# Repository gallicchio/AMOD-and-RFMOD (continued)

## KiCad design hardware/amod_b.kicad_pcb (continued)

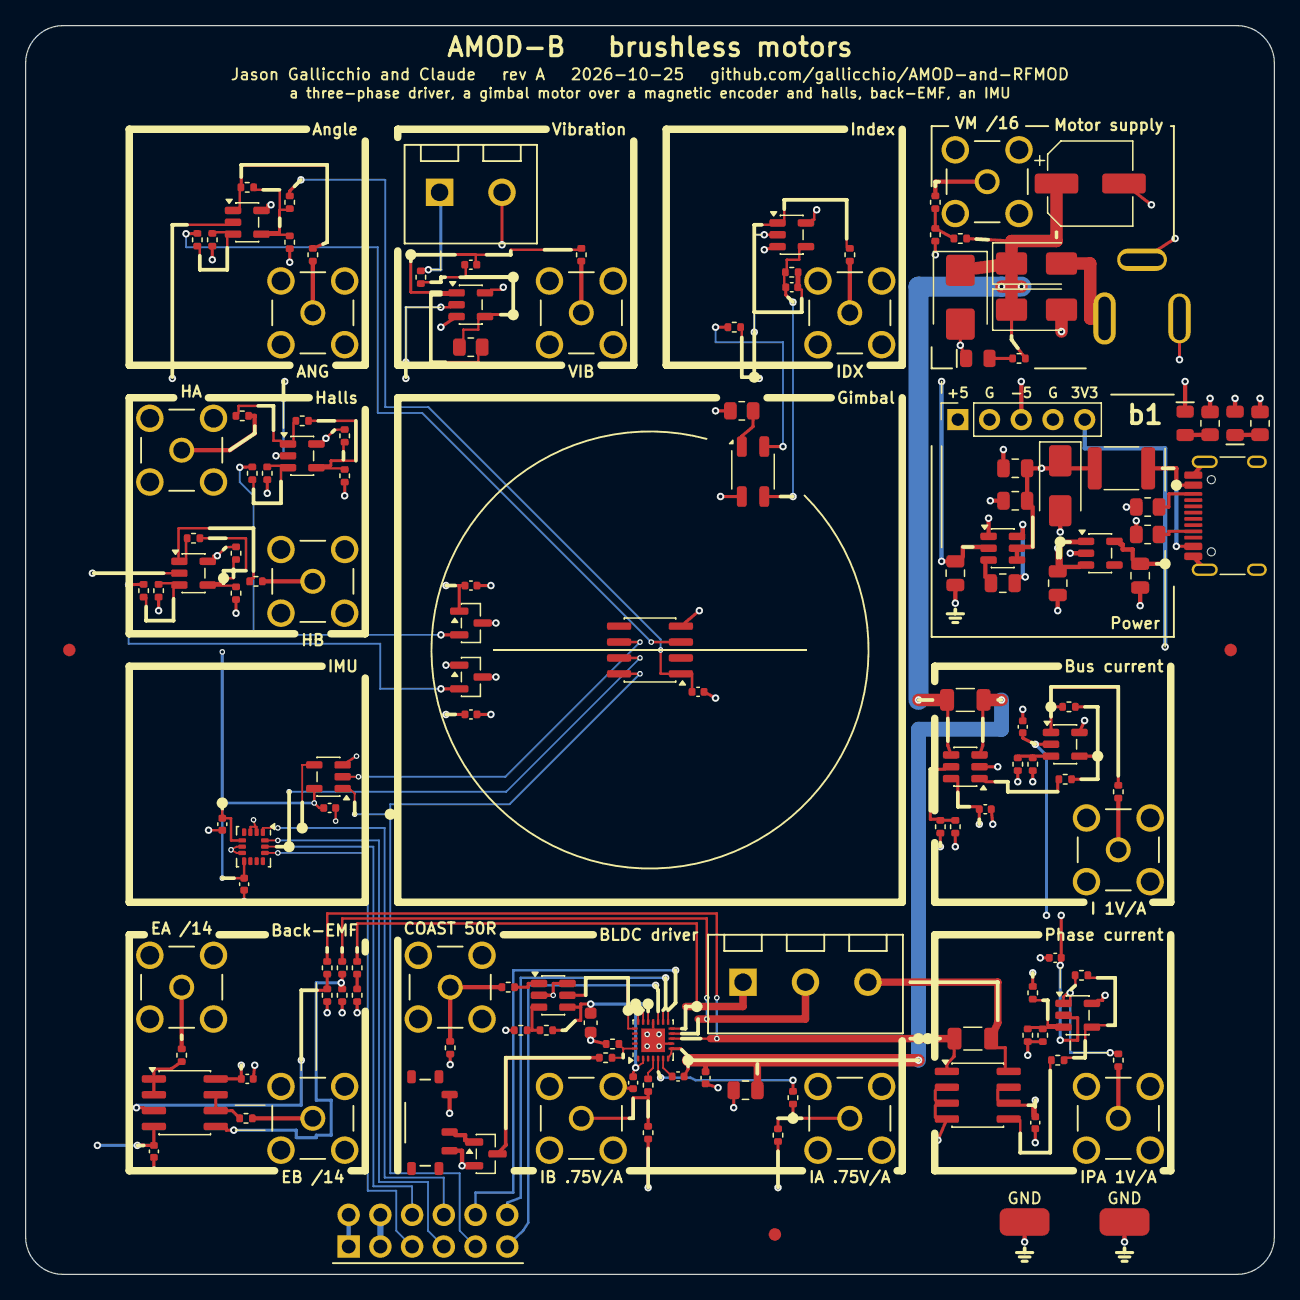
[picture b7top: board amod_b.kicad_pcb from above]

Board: 4 copper layers, 100.0 x 100.0 mm, 147 parts (0 on the bottom side), 86 nets.

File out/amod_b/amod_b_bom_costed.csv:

Comment,Designator,Footprint,LCSC Part #,MPN,Qty,Unit $,Ext $,JLC
220u,C201,CP_Elec_6.3x7.7,C2992606,XT220UF25V90RV0075,1,0.0534,0.053,extended
1u,C304,C_0603_1608Metric,C15849,CL10A105KB8NNNC,1,0.0146,0.015,basic
1n,C801,C_0402_1005Metric,C1523,0402B102K500NT,1,0.0038,0.004,basic
100p,C901,C_0402_1005Metric,C1546,0402CG101J500NT,1,0.0033,0.003,basic
1u,"C105,C106",C_0805_2012Metric,C28323,CL21B105KBFNNNE,2,0.0341,0.068,basic
10u,"C101,C102,C103,C104,C302",C_0805_2012Metric,C15850,CL21A106KAYNNNE,5,0.0426,0.213,basic
100n,"C301,C303,C305,C401,C402,C501,C502,C503,C601,C602,C603,C1101,C1102,C1201,C1202",C_0402_1005Metric,C1525,CL05B104KO5NNNC,15,0.0035,0.052,basic
SMAJ5.0A,D101,D_SMA,C78401,SMAJ5.0A,1,0.0537,0.054,extended
SMBJ12A,D201,D_SMB,C19077565,SMBJ12A,1,0.0525,0.052,preferred
SS34,"D202,D203",D_SMA,C8678,SS34,2,0.0351,0.070,basic
2A,F101,Fuse_1812_4532Metric,C210837,MF-MSMF200-2,1,0.0650,0.065,extended
USB-C,J101,USB_C_Receptacle_HRO_TYPE-C-31-M-12,C165948,TYPE-C-31-M-12,1,0.1888,0.189,extended
rails,J102,PinSocket_1x05_P2.54mm_Vertical,C2894928,PZ254-1-05-Z-8.5,1,0.0588,0.059,extended
5-12V,J202,BarrelJack_DC-005-5A_Horizontal,C381116,DC-005-5A-2.0,1,0.2631,0.263,extended
motor,J304,TerminalBlock_KF301_1x03_P5.00mm,C474882,KF301-5.0-3P,1,0.1396,0.140,extended
Pmod,J305,PinHeader_2x06_P2.54mm_Horizontal_PZ254R-12-12P,C492434,PZ254R-12-12P,1,0.1036,0.104,extended
piezo,J802,TerminalBlock_KF301_1x02_P5.00mm,C474881,KF301-5.0-2P,1,0.1017,0.102,extended
SMA,"J201,J301,J302,J303,J401,J402,J701,J801,J901,J1001,J1002,J1101,J1201",SMA_BWSMA-KE-Z001_Vertical,C496549,BWSMA-KE-Z001,13,0.4043,5.256,extended
-5V,LED101,LED_0805_2012Metric_Kbar,C84256,NCD0805R1,1,0.0135,0.013,basic
+5V,LED102,LED_0805_2012Metric_Kbar,C2297,KT-0805G,1,0.0164,0.016,basic
VM,LED201,LED_0805_2012Metric_Kbar,C2297,KT-0805G,1,0.0164,0.016,basic
AO3401A,Q301,SOT-23,C15127,AO3401A,1,0.0959,0.096,basic
15k,R203,R_0402_1005Metric,C25756,0402WGF1502TCE,1,0.0010,0.001,basic
47k,R304,R_0402_1005Metric,C25792,0402WGF4702TCE,1,0.0020,0.002,basic
100k,R306,R_0402_1005Metric,C25741,0402WGF1003TCE,1,0.0015,0.002,basic
180,R501,R_0805_2012Metric,C25270,0805W8F1800T5E,1,0.0031,0.003,extended
1M,R802,R_0805_2012Metric,C17514,0805W8F1004T5E,1,0.0038,0.004,basic
100,R902,R_0402_1005Metric,C25076,0402WGF1000TCE,1,0.0012,0.001,basic
0.05,R1101,R_1206_3216Metric,C127691,1206W3F500MT5E,1,0.0110,0.011,extended
0.1,R1201,R_1206_3216Metric,C25334,1206W4F100LT5E,1,0.0080,0.008,basic
2k,R1207,R_0402_1005Metric,C4109,0402WGF2001TCE,1,0.0026,0.003,basic
5.1k,"R101,R102",R_0805_2012Metric,C27834,0805W8F5101T5E,2,0.0036,0.007,basic
1k,"R103,R104",R_0805_2012Metric,C17513,0805W8F1001T5E,2,0.0035,0.007,basic
4.7k,"R204,R901",R_0402_1005Metric,C25900,0402WGF4701TCE,2,0.0021,0.004,basic
3.3k,"R307,R309",R_0402_1005Metric,C25890,0402WGF3301TCE,2,0.0036,0.007,basic
5.1k,"R702,R705",R_0402_1005Metric,C25905,0402WGF5101TCE,2,0.0023,0.005,basic
13k,"R401,R403,R405",R_0402_1005Metric,C25754,0402WGF1302TCE,3,0.0023,0.007,extended
3.9k,"R1002,R1005,R1008,R1011",R_0402_1005Metric,C51721,0402WGF3901TCE,4,0.0012,0.005,extended
1k,"R202,R402,R404,R406,R801,R1202,R1203",R_0402_1005Metric,C11702,0402WGF1001TCE,7,0.0013,0.009,basic
20k,"R703,R704,R1003,R1004,R1009,R1010,R1104,R1105,R1204",R_0402_1005Metric,C25765,0402WGF2002TCE,9,0.0011,0.010,basic
49.9,"R201,R301,R407,R408,R706,R803,R903,R1006,R1012,R1107,R1208",R_0402_1005Metric,C844112,CRCW040249R9FKEDHP,11,0.0318,0.350,extended
10k,"R302,R303,R305,R308,R310,R701,R1001,R1007,R1102,R1103,R1106,R1205,R1206",R_0402_1005Metric,C25744,0402WGF1002TCE,13,0.0011,0.014,basic
ON,SW301,SW_SPDT_Shouhan_MSK12C02,C431540,MSK12C02,1,0.0529,0.053,extended
GND,"TP9901,TP9902",TestPoint_Loop_RH-5019,C5199800,RH-5019,2,0.0966,0.193,extended
LM2664,U101,SOT-23-6,C108573,LM2664M6X/NOPB,1,0.3346,0.335,extended
3.3V,U102,SOT-23-5,C2862740,TPS7A2033PDBVR,1,0.2097,0.210,extended
DRV8311H,U301,Texas_RRW0024A_WQFN-24-1EP_3x3mm_P0.4mm_EP1.9x1.9mm,C5218862,DRV8311HRRWR,1,1.3773,1.377,extended
TLV3501,U302,SOT-23-6,C193413,TLV3501AIDBVR,1,1.9246,1.925,extended
OPA2171,U401,SOIC-8_3.9x4.9mm_P1.27mm,C40904,OPA2171AIDR,1,0.3423,0.342,extended
MT6701,U501,SOIC-8_3.9x4.9mm_P1.27mm,C3003196,MT6701CT-STD-R,1,1.7343,1.734,extended
QRE1113,U504,OnSemi_CASE100CY,C232862,QRE1113GR,1,0.7354,0.735,extended
LSM6DSO,U601,LGA-14_3x2.5mm_P0.5mm_LayoutBorder3x4y,C2655100,LSM6DSOTR,1,3.9926,3.993,extended
74LVC1G125,U602,SOT-23-5,C23654,SN74LVC1G125DBVR,1,0.0667,0.067,extended
INA240,U1101,SOIC-8_3.9x4.9mm_P1.27mm,C2060769,INA240A1DR,1,0.9008,0.901,extended
INA181,U1201,SOT-23-6,C2058943,INA181A1IDBVR,1,0.4717,0.472,extended
DRV5055,"U502,U503",SOT-23,C266128,DRV5055A3QDBZR,2,0.5241,1.048,extended
OPA810,"U701,U801,U901,U1001,U1002,U1102,U1202",SOT-23-5,C2833513,OPA810IDBVR,7,3.0996,21.697,extended
